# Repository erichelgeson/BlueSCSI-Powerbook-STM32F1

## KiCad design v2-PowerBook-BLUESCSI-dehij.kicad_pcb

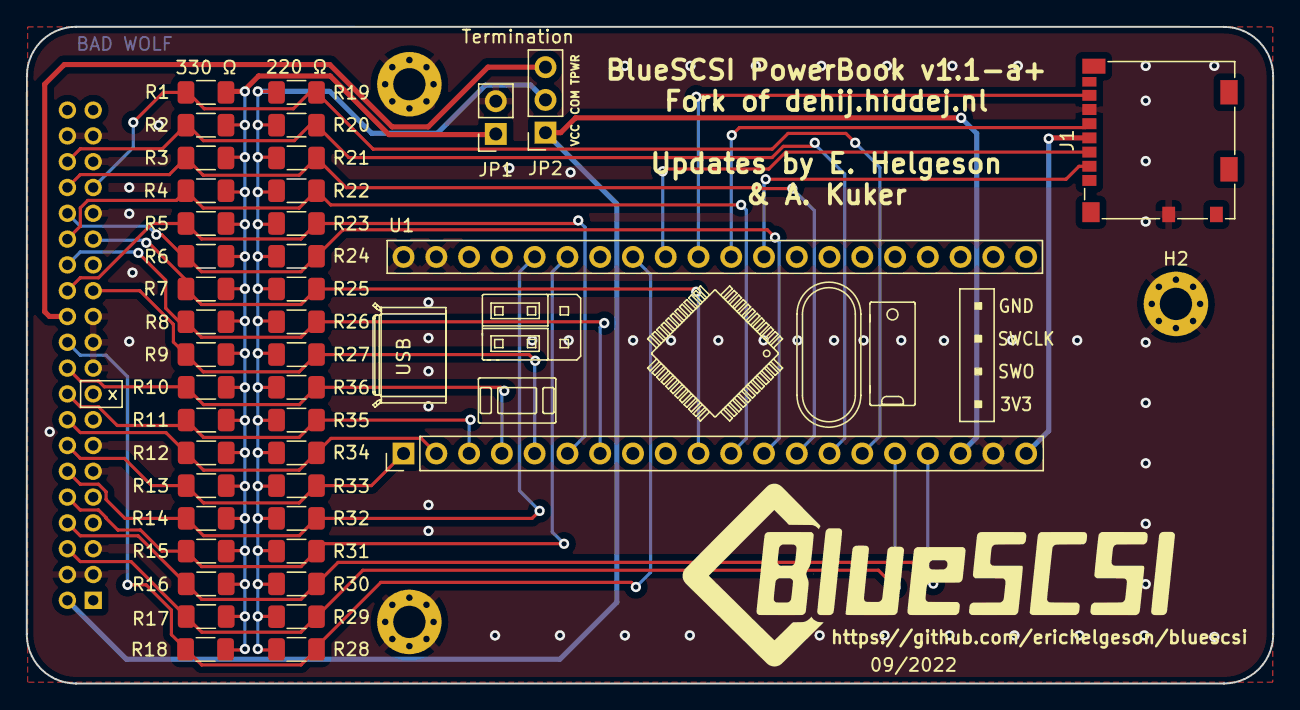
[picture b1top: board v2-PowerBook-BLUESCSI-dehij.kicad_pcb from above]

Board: 2 copper layers, 96.6 x 50.9 mm, 44 parts (1 on the bottom side), 28 nets.

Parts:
H1, H2, H3: MountingHole_Pad; MountingHole_2.5mm_Pad_Via
J1: Micro_SD_Card; 3d_MODEL_microSD_HC_Molex_104031-0811
J2: Conn_02x20_Odd_Even; PinSocket_2x20_P2.00mm_Vertical
JP1: TERM_ENABLE_GND; PinSocket_1x02_P2.54mm_Vertical
JP2: TERM_VCC_ENABLE; PinSocket_1x03_P2.54mm_Vertical
R1, R2, R3, R4, R5, R6, R7, R8, R9, R10, R11, R12, R13, R14, R15, R16, R17, R18: 330; R_1206_3216Metric_Pad1.30x1.75mm_HandSolder
R19, R20, R21, R22, R23, R24, R25, R26, R27, R28, R29, R30, R31, R32, R33, R34, R35, R36: 220; R_1206_3216Metric_Pad1.30x1.75mm_HandSolder
U1: YAAJ_BluePill_Part_Like; YAAJ_BluePill_1

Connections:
+3V3: J1.4 (VDD), U1.20 (3V3)
/SCSI_ACK: J2.28, R8.2, R26.2, U1.7 (PA10)
/SCSI_ATN: J2.25, R9.2, R27.2, U1.5 (PA8)
/SCSI_BSY: J2.26, R5.2, R23.2, U1.6 (PA9)
/SCSI_CD: J2.34, R3.2, R21.2, U1.13 (PB5)
/SCSI_DAT0: J2.6, R17.2, R29.2, U1.16 (PB8)
/SCSI_DAT1: J2.8, R16.2, R30.2, U1.17 (PB9)
/SCSI_DAT2: J2.10, R15.2, R31.2, U1.35 (PB10)
/SCSI_DAT3: J2.12, R14.2, R32.2, U1.36 (PB11)
/SCSI_DAT4: J2.14, R13.2, R33.2, U1.1 (PB12)
/SCSI_DAT5: J2.16, R12.2, R34.2, U1.2 (PB13)
/SCSI_DAT6: J2.18, R11.2, R35.2, U1.3 (PB14)
/SCSI_DAT7: J2.20, R10.2, R36.2, U1.4 (PB15)
/SCSI_DBP: J2.22, R18.2, R28.2, U1.33 (PB0)
/SCSI_IO: J2.33, R1.2, R19.2, U1.15 (PB7)
/SCSI_MSG: J2.30, R4.2, R22.2, U1.11 (PB3)
/SCSI_REQ: J2.36, R2.2, R20.2, U1.14 (PB6)
/SCSI_RST: J2.29, R7.2, R25.2, U1.10 (PA15)
/SCSI_SEL: J2.32, R6.2, R24.2, U1.12 (PB4)
/SD_CLK: J1.5 (CLK), U1.30 (PA5)
/SD_CS: J1.2 (DAT3/CD), U1.29 (PA4)
/SD_MISO: J1.7 (DAT0), U1.31 (PA6)
/SD_MOSI: J1.3 (CMD), U1.32 (PA7)
/TERM_PWR: J2.24, JP2.3 (B)
GND: H1.1, H2.1, H3.1, J1.6 (VSS), J1.9 (SHIELD), J2.3, J2.4, J2.5, J2.7, J2.9, J2.11, J2.13, J2.15, J2.19, J2.21, J2.23, J2.27, J2.31, J2.35, J2.37, J2.38, JP1.2 (B), U1.19 (GND), U1.39 (GND), U1.40 (GND)
unnamed: JP2.2 (C), R19.1, R20.1, R21.1, R22.1, R23.1, R24.1, R25.1, R26.1, R27.1, R28.1, R29.1, R30.1, R31.1, R32.1, R33.1, R34.1, R35.1, R36.1
unnamed: JP1.1 (A), R1.1, R2.1, R3.1, R4.1, R5.1, R6.1, R7.1, R8.1, R9.1, R10.1, R11.1, R12.1, R13.1, R14.1, R15.1, R16.1, R17.1, R18.1
VCC: J2.2, JP2.1 (A), U1.18 (5V)

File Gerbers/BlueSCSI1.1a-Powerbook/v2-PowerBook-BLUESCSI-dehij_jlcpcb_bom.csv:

Comment,Designator,Footprint,LCSC
"MountingHole_Pad","H1,H2,H3","MountingHole:MountingHole_2.5mm_Pad_Via",""
"Micro_SD_Card","J1","Other footprints:3d_MODEL_microSD_HC_Molex_104031-0811","C585350"
"Conn_02x20_Odd_Even","J2","Connector_PinSocket_2.00mm:PinSocket_2x20_P2.00mm_Vertical",""
"TERM_ENABLE_GND","JP1","Connector_PinSocket_2.54mm:PinSocket_1x02_P2.54mm_Vertical",""
"TERM_VCC_ENABLE","JP2","Connector_PinSocket_2.54mm:PinSocket_1x03_P2.54mm_Vertical",""
"330","R1,R2,R3,R4,R5,R6,R7,R8,R9,R10,R11,R12,R13,R14,R15,R16,R17,R18","Resistor_SMD:R_1206_3216Metric_Pad1.30x1.75mm_HandSolder","C17930"
"220","R19,R20,R21,R22,R23,R24,R25,R26,R27,R28,R29,R30,R31,R32,R33,R34,R35,R36","Resistor_SMD:R_1206_3216Metric_Pad1.30x1.75mm_HandSolder","C17957"
"YAAJ_BluePill_Part_Like","U1","Footprints:YAAJ_BluePill_1",""

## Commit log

2022-06-30 Moved resistors to 2 lines added silk screen rounded corners changed sd card
2022-06-30 Add gerbers for 1.1a
2022-09-09 Tonys Updates
